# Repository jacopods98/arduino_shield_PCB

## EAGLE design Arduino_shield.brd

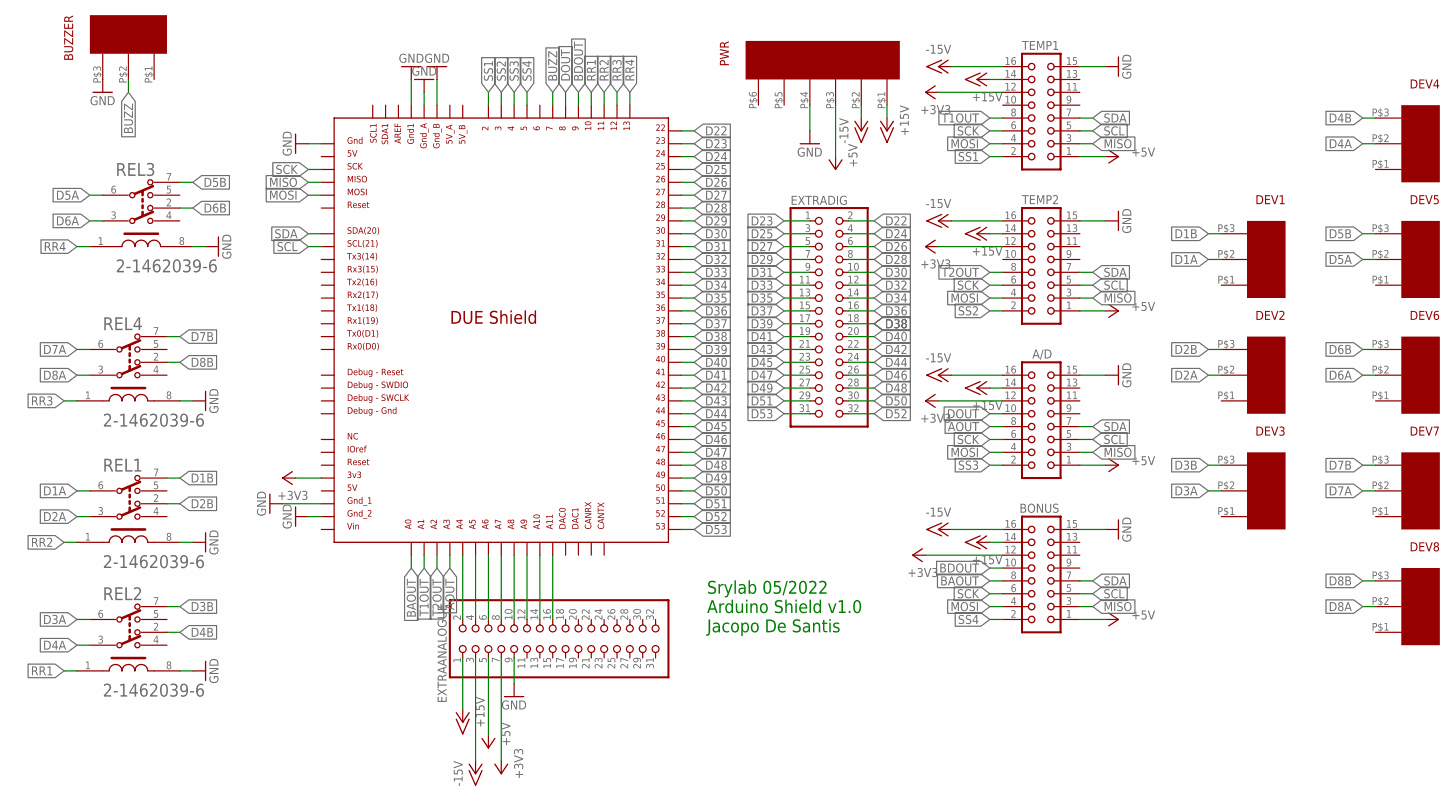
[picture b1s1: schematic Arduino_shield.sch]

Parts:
A/D: CON16L
BONUS: CON16L
BUZZER: 3PIN_CON
DEV1, DEV2, DEV3, DEV4, DEV5, DEV6, DEV7, DEV8: 3PIN_CON
EXTRAANALOGUE: PINHD-2X16; 2X16
EXTRADIG: PINHD-2X16; 2X16
PWR: 6PIN_CON
REL1, REL2, REL3, REL4: TE_2-1462039-6TE_2-1462039-6_0_0; TE_2-1462039-6_0
TEMP1, TEMP2: CON16L
U$1: DUE(NORMAL)

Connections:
+3V3: A/D.12, BONUS.12, EXTRAANALOGUE.7, TEMP1.12, TEMP2.12, U$1.3V3
+5V: A/D.1, BONUS.1, EXTRAANALOGUE.5, PWR.P$3, TEMP1.1, TEMP2.1
+15V: A/D.14, BONUS.14, EXTRAANALOGUE.1, PWR.P$1, TEMP1.14, TEMP2.14
-15V: A/D.16, BONUS.16, EXTRAANALOGUE.3, PWR.P$2, TEMP1.16, TEMP2.16
AOUT: A/D.8, U$1.A3
BAOUT: BONUS.8, U$1.A0
BDOUT: BONUS.10, U$1.9
BUZZ: BUZZER.P$2, U$1.7
D1A: DEV1.P$2, REL1.6
D1B: DEV1.P$3, REL1.7
D2A: DEV2.P$2, REL1.3
D2B: DEV2.P$3, REL1.2
D3A: DEV3.P$2, REL2.6
D3B: DEV3.P$3, REL2.7
D4A: DEV4.P$2, REL2.3
D4B: DEV4.P$3, REL2.2
D5A: DEV5.P$2, REL3.6
D5B: DEV5.P$3, REL3.7
D6A: DEV6.P$2, REL3.3
D6B: DEV6.P$3, REL3.2
D7A: DEV7.P$2, REL4.6
D7B: DEV7.P$3, REL4.7
D8A: DEV8.P$2, REL4.3
D8B: DEV8.P$3, REL4.2
D22: EXTRADIG.2, U$1.22
D23: EXTRADIG.1, U$1.23
D24: EXTRADIG.4, U$1.24
D25: EXTRADIG.3, U$1.25
D26: EXTRADIG.6, U$1.26
D27: EXTRADIG.5, U$1.27
D28: EXTRADIG.8, U$1.28
D29: EXTRADIG.7, U$1.29
D30: EXTRADIG.10, U$1.30
D31: EXTRADIG.9, U$1.31
D32: EXTRADIG.12, U$1.32
D33: EXTRADIG.11, U$1.33
D34: EXTRADIG.14, U$1.34
D35: EXTRADIG.13, U$1.35
D36: EXTRADIG.16, U$1.36
D37: EXTRADIG.15, U$1.37
D38: EXTRADIG.18, U$1.38
D39: EXTRADIG.17, U$1.39
D40: EXTRADIG.20, U$1.40
D41: EXTRADIG.19, U$1.41
D42: EXTRADIG.22, U$1.42
D43: EXTRADIG.21, U$1.43
D44: EXTRADIG.24, U$1.44
D45: EXTRADIG.23, U$1.45
D46: EXTRADIG.26, U$1.46
D47: EXTRADIG.25, U$1.47
D48: EXTRADIG.28, U$1.48
D49: EXTRADIG.27, U$1.49
D50: EXTRADIG.30, U$1.50
D51: EXTRADIG.29, U$1.51
D52: EXTRADIG.32, U$1.52
D53: EXTRADIG.31, U$1.53
DOUT: A/D.10, U$1.8
GND: A/D.15, BONUS.15, BUZZER.P$3, EXTRAANALOGUE.9, PWR.P$4, REL1.8, REL2.8, REL3.8, REL4.8, TEMP1.15, TEMP2.15, U$1.5V_ICSP, U$1.GND1, U$1.GND_1, U$1.GND_2, U$1.GND_A, U$1.GND_B
MISO: A/D.3, BONUS.3, TEMP1.3, TEMP2.3, U$1.MISO_ICSP
MOSI: A/D.4, BONUS.4, TEMP1.4, TEMP2.4, U$1.MOSI_ICSP
unnamed: EXTRAANALOGUE.2, U$1.A4
unnamed: EXTRAANALOGUE.4, U$1.A5
unnamed: EXTRAANALOGUE.6, U$1.A6
unnamed: EXTRAANALOGUE.8, U$1.A7
unnamed: EXTRAANALOGUE.10, U$1.A8
unnamed: EXTRAANALOGUE.12, U$1.A9
unnamed: EXTRAANALOGUE.14, U$1.A10
unnamed: EXTRAANALOGUE.16, U$1.A11
RR1: REL2.1, U$1.10
RR2: REL1.1, U$1.11
RR3: REL4.1, U$1.12
RR4: REL3.1, U$1.13
SCK: A/D.6, BONUS.6, TEMP1.6, TEMP2.6, U$1.SCK_ICSP
SCL: A/D.5, BONUS.5, TEMP1.5, TEMP2.5, U$1.SCL
SDA: A/D.7, BONUS.7, TEMP1.7, TEMP2.7, U$1.SDA
SS1: TEMP1.2, U$1.2
SS2: TEMP2.2, U$1.3
SS3: A/D.2, U$1.4
SS4: BONUS.2, U$1.5
T1OUT: TEMP1.8, U$1.A1
T2OUT: TEMP2.8, U$1.A2

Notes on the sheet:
Srylab 05/2022 Arduino Shield v1.0 Jacopo De Santis

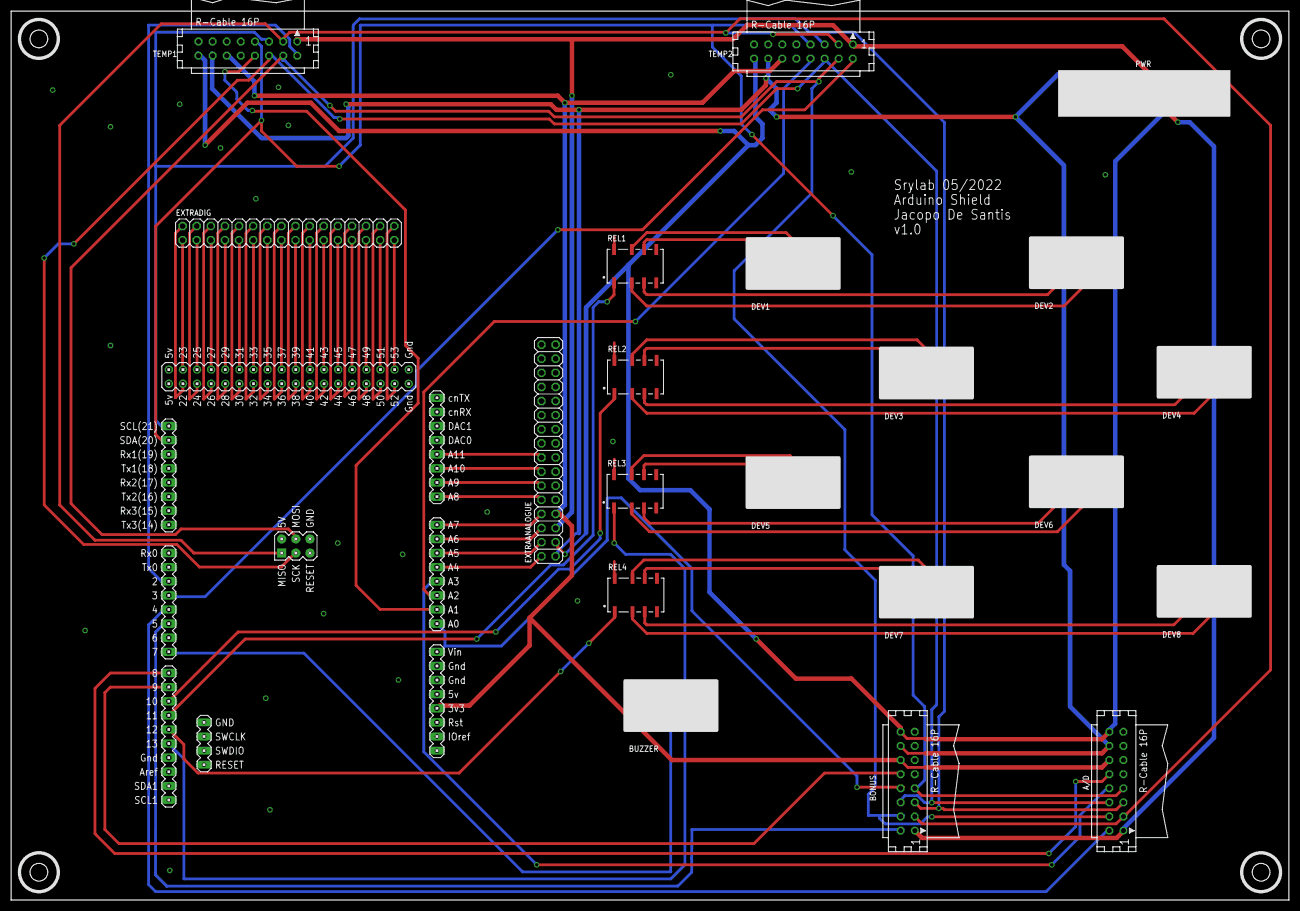
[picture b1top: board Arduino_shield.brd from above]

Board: 2 copper layers, 230.0 x 160.0 mm, 21 parts (0 on the bottom side), 81 nets.

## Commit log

2022-03-10 initialization
2022-03-10 Schematics_v1
2022-03-10 Official_flat_cable_connections
2022-03-11 Added_relays
2022-03-11 Final_v1
2022-03-11 Board_init
2022-03-16 Initial_handmade_routing
2022-03-17 finished_autorouting_no_rules
2022-03-17 finished_autorouting_no_rules_1
2022-03-17 autorouted_with_rules
2022-03-17 finished_ruled_autorouting
2022-03-22 final_print
2022-03-23 ready_to_print
2022-06-08 production
